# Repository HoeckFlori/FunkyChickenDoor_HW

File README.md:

# FunkyChickenDoor_HW

In this repository the **electronic hardware** for the 'Funky Chicken Door' [project](https://github.com/HoeckFlori/FunkyChickenDoor_SW) is/was developed.

The idea is, to develop a automatic chicken-house-door-controller and provide it on a semi-professional level with simple, available and inexpensive components. For detailed information about the features, the usage and anything else, have a look into the [corresponding software repo](https://github.com/HoeckFlori/FunkyChickenDoor_SW).

The circuit diagrams and PCB is drawn with [KiCad](https://kicad.org/) and can be opened and edited at any time with it.

You can build up the hardware as strip board solution or order a PCB from your preferred PCB dealer.  

<details>
  <summary>'development stripboard solution'</summary>

</details>

If you want want to use the hardware you can rebuild it for your private stuff. A BOM with the order codes to an German electronic distributor is attached. Nevertheless some 'specialized' components are needed. Look below.

In case of problems, errors or suggestions for improvement, please send me an issue.

# Quick links within the repository
## KiCad project
[KiCadProject](./AMShieldV1/ChickenDoor_V1.pro)

## Schematic
[Schematic](./AMShieldV1/ChickenDoor_V1_1-0-0_Schematic.pdf)

## Assembly print
[Assembly print](./AMShieldV1/ChickenDoor_V1_1-0-0_AssemblyPrint.pdf)

## BOM (bill of materials)
[Schematic](./AMShieldV1/ChickenDoor_V1_1-0-0_BOM_withReicheltOrderCodes.ods)

## Pictures of the PCB
<details>
  <summary>Click me to see some screenshots</summary>

![](./AMShieldV1/ChickenDoor_V1_PCB_view02_side%20right.png

</details>

## The more 'specialized' components you need to get

<details>
  <summary>'click me to open the list'</summary>

| What                                                     | Link to further information and (possible) vendors                                                                                                                                                                                                                                                                                                                                               | Detailed information                                                                                                                                                                                                                                                                                                                                                                                                                                                                                                                                                                                                            | Realistic price (from a well-known auction platform with longer shipping time), mid 2020 |
| -------------------------------------------------------- | ------------------------------------------------------------------------------------------------------------------------------------------------------------------------------------------------------------------------------------------------------------------------------------------------------------------------------------------------------------------------------------------------ | ------------------------------------------------------------------------------------------------------------------------------------------------------------------------------------------------------------------------------------------------------------------------------------------------------------------------------------------------------------------------------------------------------------------------------------------------------------------------------------------------------------------------------------------------------------------------------------------------------------------------------- | ---------------------------------------------------------------------------------------- |
| MCU Board 'Mega 2560 PRO (Embed) CH340G/ATmega2560-16AU' | [https://robotdyn.com/mega-2560-pro-embed-ch340g-atmega2560-16au.html](https://robotdyn.com/mega-2560-pro-embed-ch340g-atmega2560-16au.html) or [https://www.reichelt.de/at/en/arduino-compatible-mega-2560-pro-board-ard-mega2560-pro-p299355.html?&trstct=pos_0&nbc=1](https://www.reichelt.de/at/en/arduino-compatible-mega-2560-pro-board-ard-mega2560-pro-p299355.html?&trstct=pos_0&nbc=1) | <ul><li>[Dimensional drawing](https://robotdyn.com/pub/media/0G-00005641==MEGA-PRO-CH340GATmega2560/DOCS/DIM==0G-00005641==MEGA-PRO-CH340GATmega2560.pdf)</li><li>[Input and Output I/O diagram](https://robotdyn.com/pub/media/0G-00005641==MEGA-PRO-CH340GATmega2560/DOCS/PINOUT==0G-00005641==MEGA-PRO-CH340GATmega2560.pdf)</li><li>[Schematic](https://robotdyn.com/pub/media/0G-00005641==MEGA-PRO-CH340GATmega2560/DOCS/Schematic==0G-00005641==MEGA-PRO-CH340GATmega2560.pdf)</li></ul>                                                                                                                                 | ~ 7,- €                                                                                  |
| RTC DS3231 I2C AT24C32 Real Time Clock                   | https://www.makershop.de/module/rtc/rtc-ds3231-i2c/                                                                                                                                                                                                                                                                                                                                              | [Interface DS3231 Precision RTC Module with Arduino](https://lastminuteengineers.com/ds3231-rtc-arduino-tutorial/)                                                                                                                                                                                                                                                                                                                                                                                                                                                                                                              | ~ 3,- €                                                                                  |
| 1,8 Zoll TFT LCD Display Modul 128×160                   | [https://www.amazon.com/HiLetgo-ST7735R-128160-Display-Arduino/dp/B00LSG51MM](https://www.amazon.com/HiLetgo-ST7735R-128160-Display-Arduino/dp/B00LSG51MM) or [https://www.makershop.de/display/lcd-tft/waveshare-1-8inch-lcd-modul/](https://www.makershop.de/display/lcd-tft/waveshare-1-8inch-lcd-modul/)                                                                                     | Try to get a display like in the link! The market is full of displays of this type, but each one has other connectors, dimensions, orientations, ... .<br/> Some may interesting links:<br/> [1.8" Serial SPI 128x160 Color TFT LCD Module Display](https://www.openhacks.com/uploadsproductos/tutorial_display_tft.pdf),<br/> [https://learn.adafruit.com/1-8-tft-display/breakout-pinouts](https://learn.adafruit.com/1-8-tft-display/breakout-pinouts),<br/> [Arduino Tutorial: Making the KMR-1.8 SPI (TFT Display) work!](https://www.mschoeffler.de/2019/06/20/arduino-tutorial-making-the-kmr-1-8-spi-tft-display-work/) | ~ 8,-€ <br/> (on a well-known internet auction house)                                    |

</details>

# FAQ
Currently nothing :smiley:

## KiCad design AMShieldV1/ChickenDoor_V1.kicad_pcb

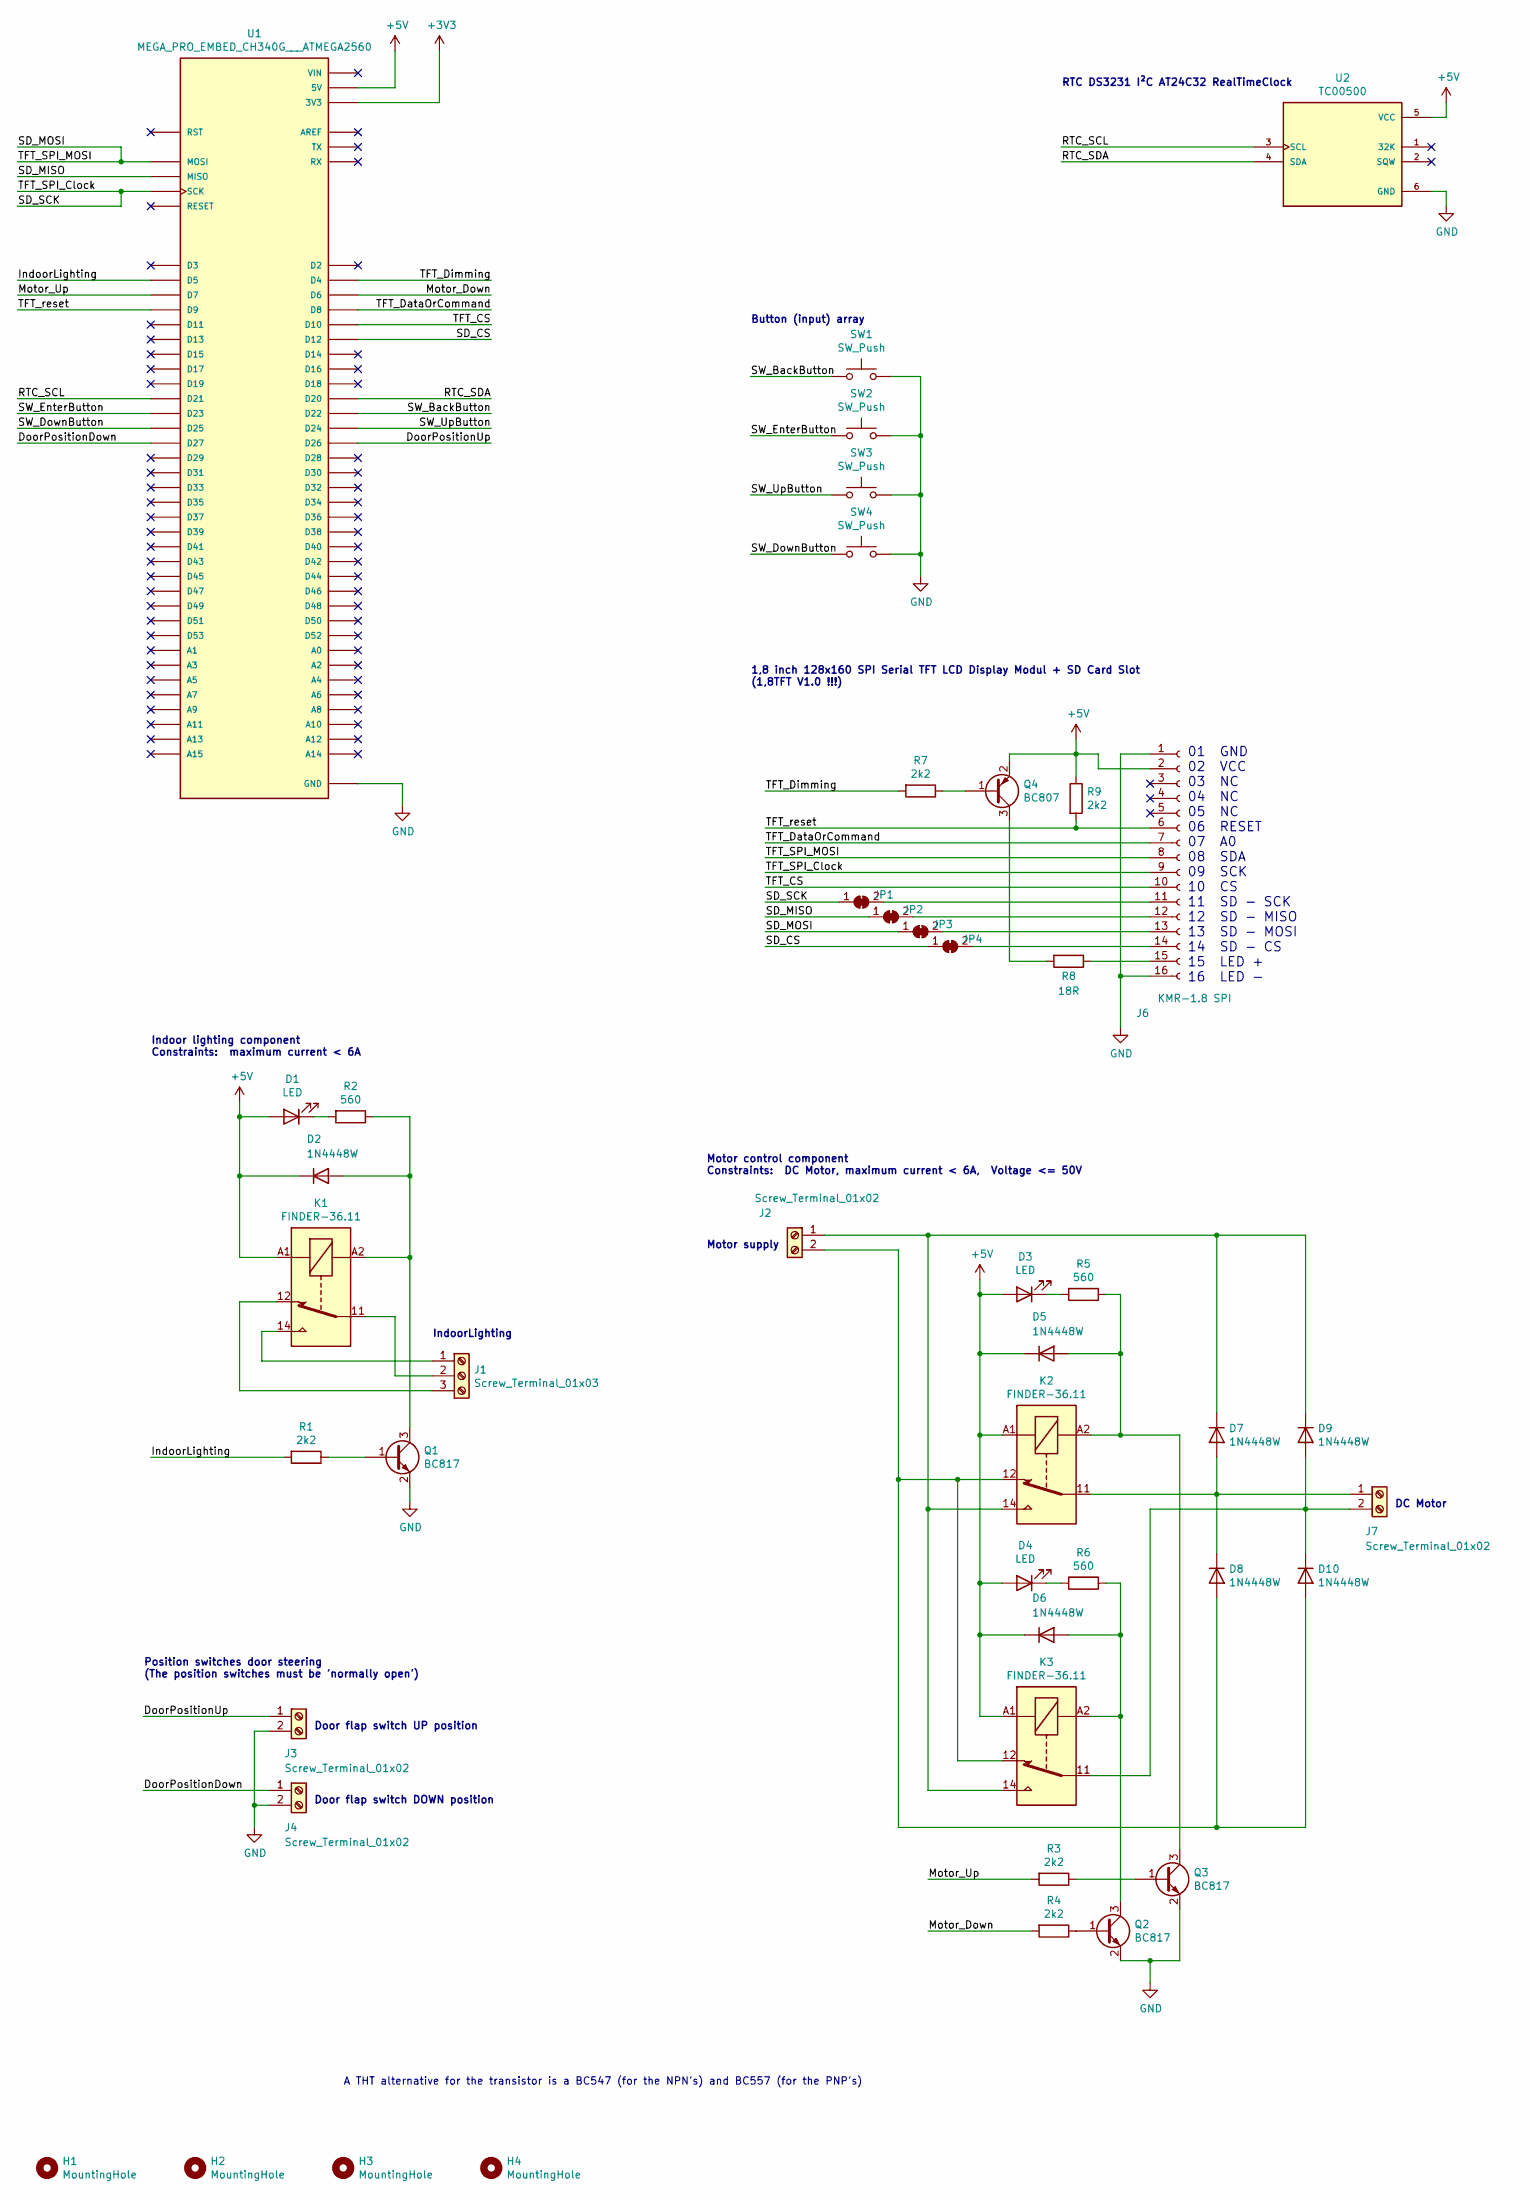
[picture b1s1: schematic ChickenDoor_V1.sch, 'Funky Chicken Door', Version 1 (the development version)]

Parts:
D1, D3, D4: LED; LED_1206_3216Metric
D2, D5, D6, D7, D8, D9, D10: 1N4448W; D_SOD-123
H1, H2, H3, H4: MountingHole; MountingHole_4.3mm_M4_DIN965
J1: Screw_Terminal_01x03; TerminalBlock_Phoenix_MKDS-1,5-3-5.08_1x03_P5.08mm_Horizont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
J2, J3, J4, J7: Screw_Terminal_01x02; TerminalBlock_Phoenix_MKDS-1,5-2-5.08_1x02_P5.08mm_Horizont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
J6: KMR-1.8 SPI; KMR-1.8-SPI
JP1, JP2, JP3, JP4: SolderJumper_2_Bridged; SolderJumper-2_P1.3mm_Bridged_RoundedPad1.0x1.5mm
K1, K2, K3: FINDER-36.11; Relay_SPDT_Finder_36.11
Q1, Q2, Q3: BC817; SOT-23
Q4: BC807; SOT-23
R1, R3, R4, R7, R9: 2k2; R_0805_2012Metric
R2, R5, R6: 560; R_0805_2012Metric
R8: 18R; R_0805_2012Metric
SW1, SW2, SW3, SW4: SW_Push; SW_PUSH_6mm_H9.5mm
U1: MEGA_PRO_EMBED_CH340G___ATMEGA2560; MODULE_MEGA_PRO_EMBED_CH340G___ATMEGA2560; PARTREV 12/May/2017
U2: TC00500; MODULE_TC00500_FHk_BatteryUpside; PARTREV N/A

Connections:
+3V3: U1.3V3_1 (3V3), U1.3V3_2 (3V3)
+5V: D1.2 (A), D2.1 (K), D3.2 (A), D4.2 (A), D5.1 (K), D6.1 (K), J6.2, K1.A1, K2.A1, K3.A1, Q4.2 (E), R9.1, U1.5V_1 (5V), U1.5V_2 (5V), U1.5V_3 (5V), U2.5 (VCC)
/DoorPositionDown: J4.1, U1.D27
/DoorPositionUp: J3.1, U1.D26
/IndoorLighting: R1.2, U1.D5
/Motor_Down: R4.2, U1.D6
/Motor_Up: R3.2, U1.D7
/RTC_SCL: U1.D21, U2.3 (SCL)
/RTC_SDA: U1.D20, U2.4 (SDA)
/SD_CS: JP4.1 (A), U1.D12
/SD_MISO: JP2.1 (A), U1.MISO
/SD_MOSI: J6.8, JP3.1 (A), U1.MOSI
/SD_SCK: J6.9, JP1.1 (A), U1.SCK
/SW_BackButton: SW1.1, U1.D22
/SW_DownButton: SW4.1, U1.D25
/SW_EnterButton: SW2.1, U1.D23
/SW_UpButton: SW3.1, U1.D24
/TFT_CS: J6.10, U1.D10
/TFT_DataOrCommand: J6.7, U1.D8
/TFT_Dimming: R7.2, U1.D4
/TFT_reset: J6.6, R9.2, U1.D9
GND: J3.2, J4.2, J6.1, J6.16, Q1.2 (E), Q2.2 (E), Q3.2 (E), SW1.2, SW2.2, SW3.2, SW4.2, U1.GND_1 (GND), U1.GND_2 (GND), U1.GND_3 (GND), U2.6 (GND)
unnamed: D1.1 (K), R2.2
unnamed: D2.2 (A), K1.A2, Q1.3 (C), R2.1
unnamed: D3.1 (K), R5.2
unnamed: D4.1 (K), R6.2
unnamed: D5.2 (A), K2.A2, Q3.3 (C), R5.1
unnamed: D6.2 (A), K3.A2, Q2.3 (C), R6.1
unnamed: D7.1 (K), D9.1 (K), J2.1, K2.14, K3.14
unnamed: D7.2 (A), D8.1 (K), J7.1, K2.11
unnamed: D9.2 (A), D10.1 (K), J7.2, K3.11
unnamed: D8.2 (A), D10.2 (A), J2.2, K2.12, K3.12
unnamed: J1.1, K1.14
unnamed: J1.2, K1.11
unnamed: J1.3, K1.12
unnamed: J6.11, JP1.2 (B)
unnamed: J6.12, JP2.2 (B)
unnamed: J6.13, JP3.2 (B)
unnamed: J6.14, JP4.2 (B)
unnamed: J6.15, R8.1
unnamed: Q1.1 (B), R1.1
unnamed: Q2.1 (B), R4.1
unnamed: Q3.1 (B), R3.1
unnamed: Q4.1 (B), R7.1
unnamed: Q4.3 (C), R8.2
unnamed: U1.VIN_1 (VIN), U1.VIN_2 (VIN)

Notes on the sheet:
01 GND 02 VCC 03 NC 04 NC 05 NC 06 RESET 07 A0 08 SDA 09 SCK 10 CS 11 SD - SCK 12 SD - MISO 13 SD - MOSI 14 SD - CS 15 LED + 16 LED -
1,8 inch 128x160 SPI Serial TFT LCD Display Modul + SD Card Slot (1,8TFT V1.0 !!!)
RTC DS3231 I²C AT24C32 RealTimeClock
DC Motor
Motor supply
Door flap switch UP position
Door flap switch DOWN position
IndoorLighting
Button (input) array
Motor control component Constraints: DC Motor, maximum current < 6A, Voltage <= 50V
Indoor lighting component Constraints: maximum current < 6A
Position switches door steering (The position switches must be 'normally open')
A THT alternative for the transistor is a BC547 (for the NPN's) and BC557 (for the PNP's)

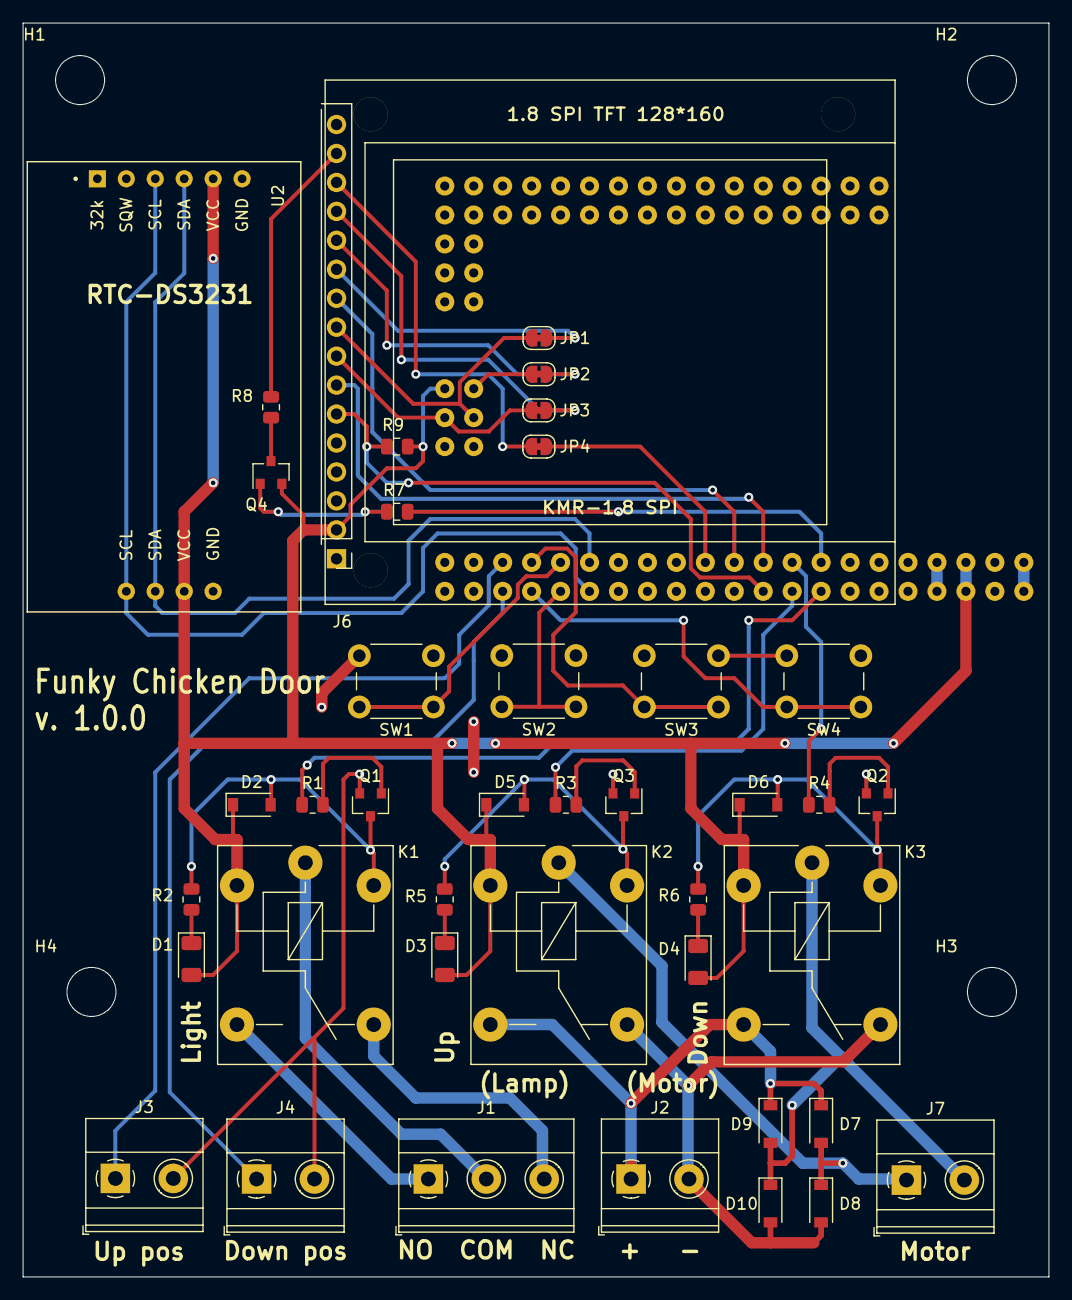
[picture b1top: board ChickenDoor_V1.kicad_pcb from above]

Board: 2 copper layers, 90.0 x 110.0 mm, 46 parts (1 on the bottom side), 46 nets.

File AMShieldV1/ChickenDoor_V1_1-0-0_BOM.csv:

"ID";"Bezeichner";"Gehäuse";"Stückzahl";"Bezeichnung";"Anbieter und Referenz";
1;"JP4,JP3,JP2,JP1";"SolderJumper-2_P1.3mm_Bridged_RoundedPad1.0x1.5mm";4;"SolderJumper_2_Bridged";;;
2;"J6";"KMR-1.8-SPI";1;"KMR-1.8 SPI";;;
3;"J7,J4,J3,J2";"TerminalBlock_Phoenix_MKDS-1,5-2-5.08_1x02_P5.08mm_Horizontal";4;"Screw_Terminal_01x02";;;
4;"J1";"TerminalBlock_Phoenix_MKDS-1,5-3-5.08_1x03_P5.08mm_Horizontal";1;"Screw_Terminal_01x03";;;
5;"U1";"MODULE_MEGA_PRO_EMBED_CH340G___ATMEGA2560";1;"MEGA_PRO_EMBED_CH340G___ATMEGA2560";;;
6;"U2";"MODULE_TC00500_FHk_BatteryUpside";1;"TC00500";;;
7;"R7,R9,R4,R3,R1";"R_0805_2012Metric";5;"2k2";;;
8;"Q4";"SOT-23";1;"BC807";;;
9;"D4,D3,D1";"LED_1206_3216Metric";3;"LED";;;
10;"Q3,Q2,Q1";"SOT-23";3;"BC817";;;
11;"D6,D5,D2,D10,D9,D8,D7";"D_SOD-123";7;"1N4448W";;;
12;"R8";"R_0805_2012Metric";1;"18R";;;
13;"R6,R5,R2";"R_0805_2012Metric";3;"560";;;
14;"H4,H3,H2,H1";"MountingHole_4.3mm_M4_DIN965";4;"MountingHole";;;
15;"K3,K2,K1";"Relay_SPDT_Finder_36.11";3;"FINDER-36.11";;;
16;"SW4,SW3,SW2,SW1";"SW_PUSH_6mm_H9.5mm";4;"SW_Push";;;

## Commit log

2020-10-10 Initial commit with the preliminary work from the existing software repository.
2020-10-10 Some readme additions.
2020-11-01 Built up the stripboard solution. Minor changes in the circuit. Updated the readme.
2020-11-01 Small readme fix
2020-11-01 Does this fix the broken table?
2020-11-01 Add missing line in readme markdown file.
2020-11-01 Markdown ...
2022-03-17 First draft of the PCB with updated schematic.
2022-03-18 All manufacturing documents added. Order sent.
2022-03-25 Minor addition to the BOM. Some cleanups.
2023-01-06 Finalized docu
